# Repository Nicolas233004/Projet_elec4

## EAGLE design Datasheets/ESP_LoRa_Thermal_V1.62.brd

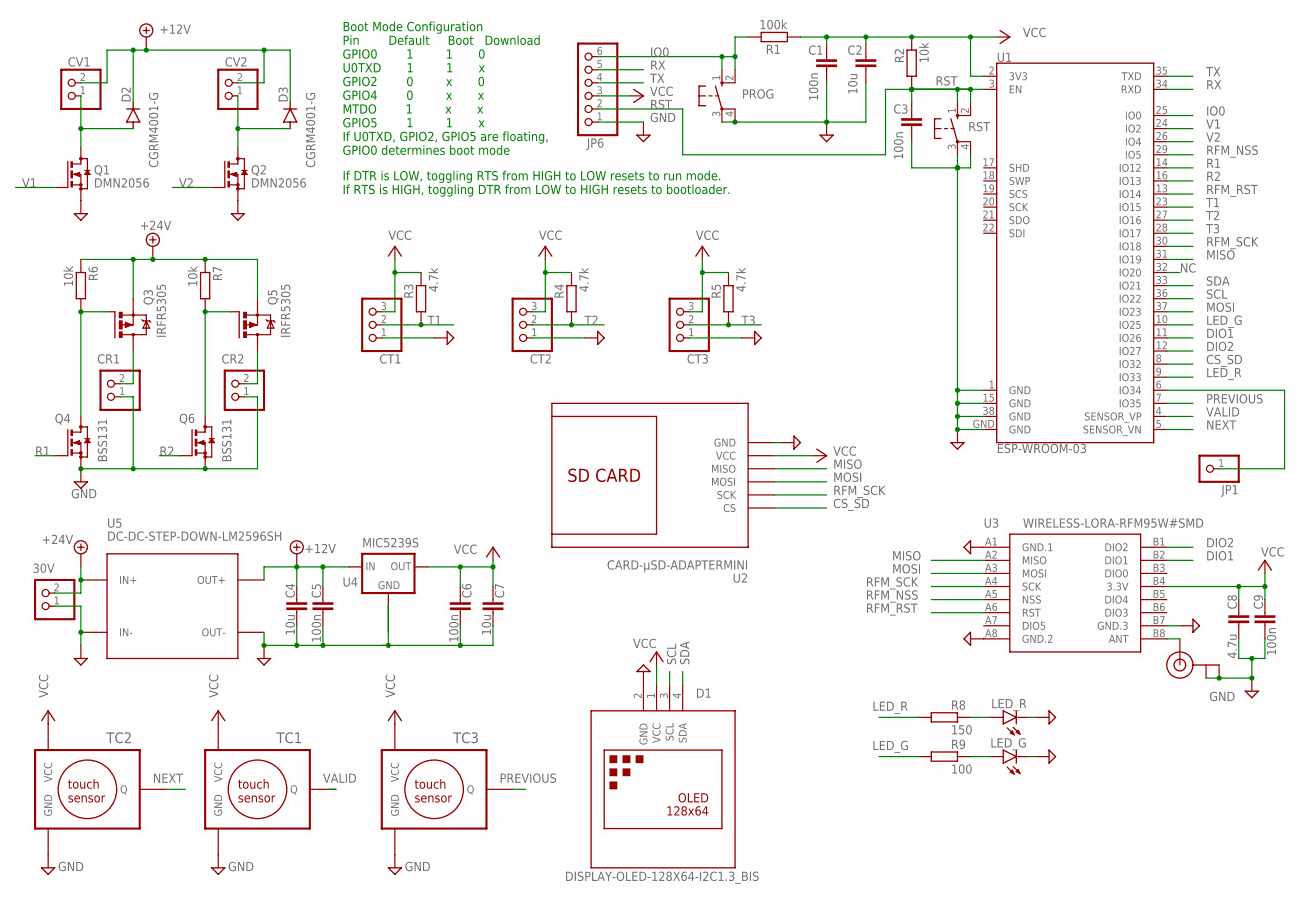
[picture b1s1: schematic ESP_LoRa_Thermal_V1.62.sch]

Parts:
30V: PINHD-1X2; 1X02
C1, C3, C5, C6, C9: 100n; C1206
C2, C4, C7: 10u; C1206
C8: 4.7u; C1206
CR1, CR2: PINHD-1X2; 1X02
CT1, CT2, CT3: PINHD-1X3; 1X03
CV1, CV2: PINHD-1X2; 1X02
D1: DISPLAY-OLED-128X64-I2C1.3_BIS; DISPLAY-OLED-128X64-1.3-I2C_BIS
D2, D3: CGRM4001-G; SOD-123_MINI-SMA
J1: U.FL
JP1: PINHD-1X1; 1X01
JP6: PINHD-1X6; 1X06
LED_G: LEDSMT1206; 1206
LED_R: LEDSMT1206; 1206
PROG: 10-XX; B3F-10XX
Q1, Q2: DMN2056; SOT23
Q3, Q5: IRFR5305; D-PAK_TO252AA
Q4, Q6: BSS131; SOT23
R1: 100k; R1206
R2, R6, R7: 10k; R1206
R3, R4, R5: 4.7k; R1206
R8: 150; R1206
R9: 100; R1206
RST: 10-XX; B3F-10XX
TC1, TC2, TC3: TTP223R_H; TTP233RED_H
U1: ESP-WROOM-03
U2: CARD-µSD-ADAPTERMINI; CARD-MINI--µSD-READER
U3: WIRELESS-LORA-RFM95W#SMD
U4: MIC5239S; SOT223
U5: DC-DC-STEP-DOWN-LM2596SH; DC-DC-STEP-DOWN-LM2596-SH

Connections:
+12V: C4.1, C5.1, CV1.2, CV2.2, D2.C, D3.C, U4.1 (IN), U5.OUT+
+24V: 30V.2, Q3.3 (S), Q5.3 (S), R6.1, R7.1, U5.IN+
ANT: J1.3 (SIGNAL), U3.B8 (ANT)
CS_SD: U1.8 (IO32), U2.CS
DIO1: U1.11 (IO26), U3.B2 (DIO1)
DIO2: U1.12 (IO27), U3.B1 (DIO2)
GND: 30V.1, C1.2, C2.2, C3.2, C4.2, C5.2, C6.2, C7.2, C8.2, C9.2, CR1.1, CR2.1, CT1.1, CT2.1, CT3.1, D1.2 (GND), J1.1 (GND), J1.2 (GND), JP6.1, LED_G.C, LED_R.C, PROG.3, PROG.4 (P1), Q1.2 (S), Q2.2 (S), Q4.2 (S), Q6.2 (S), RST.3, RST.4 (P1), TC1.P$3 (GND), TC2.P$3 (GND), TC3.P$3 (GND), U1.1 (GND), U1.15 (GND), U1.38 (GND), U1.GND, U2.GND, U3.A1 (GND.1), U3.A8 (GND.2), U3.B7 (GND.3), U4.2 (GND), U4.4 (GND), U5.IN-, U5.OUT-
IO0: JP6.6, PROG.1 (S), PROG.2 (S1), R1.2, U1.25 (IO0)
LED_G: R9.1, U1.10 (IO25)
LED_R: R8.1, U1.9 (IO33)
MISO: U1.31 (IO19), U2.MISO, U3.A2 (MISO)
MOSI: U1.37 (IO23), U2.MOSI, U3.A3 (MOSI)
unnamed: CR2.2, Q5.4 (D)
unnamed: CV1.1, D2.A, Q1.3 (D)
unnamed: CR1.2, Q3.4 (D)
unnamed: CV2.1, D3.A, Q2.3 (D)
unnamed: JP1.1, U1.6 (IO34)
unnamed: LED_R.A, R8.2
unnamed: LED_G.A, R9.2
unnamed: Q3.1 (G), Q4.3 (D), R6.2
unnamed: Q5.1 (G), Q6.3 (D), R7.2
NC: U1.32 (IO20)
NEXT: TC2.P$2 (Q), U1.5 (SENSOR_VN)
PREVIOUS: TC3.P$2 (Q), U1.7 (IO35)
R1: Q4.1 (G), U1.14 (IO12)
R2: Q6.1 (G), U1.16 (IO13)
RFM_NSS: U1.29 (IO5), U3.A5 (NSS)
RFM_RST: U1.13 (IO14), U3.A6 (RST)
RFM_SCK: U1.30 (IO18), U2.SCK, U3.A4 (SCK)
RST: C3.1, JP6.2, R2.1, RST.1 (S), RST.2 (S1), U1.3 (EN)
RX: JP6.5, U1.34 (RXD)
SCL: D1.3 (SCL), U1.36 (IO22)
SDA: D1.4 (SDA), U1.33 (IO21)
T1: CT1.2, R3.1, U1.23 (IO15)
T2: CT2.2, R4.1, U1.27 (IO16)
T3: CT3.2, R5.1, U1.28 (IO17)
TX: JP6.4, U1.35 (TXD)
V1: Q1.1 (G), U1.24 (IO2)
V2: Q2.1 (G), U1.26 (IO4)
VALID: TC1.P$2 (Q), U1.4 (SENSOR_VP)
VCC: C1.1, C2.1, C6.1, C7.1, C8.1, C9.1, CT1.3, CT2.3, CT3.3, D1.1 (VCC), JP6.3, R1.1, R2.2, R3.2, R4.2, R5.2, TC1.P$1 (VCC), TC2.P$1 (VCC), TC3.P$1 (VCC), U1.2 (3V3), U2.VCC, U3.B4 (3.3V), U4.3 (OUT)

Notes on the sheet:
If DTR is LOW, toggling RTS from HIGH to LOW resets to run mode. If RTS is HIGH, toggling DTR from LOW to HIGH resets to bootloader.
Boot Mode Configuration Pin Default Boot Download GPIO0 1 1 0 U0TXD 1 1 x GPIO2 0 x 0 GPIO4 0 x x MTDO 1 x x GPIO5 1 1 x If U0TXD, GPIO2, GPIO5 are floating, GPIO0 determines boot mode

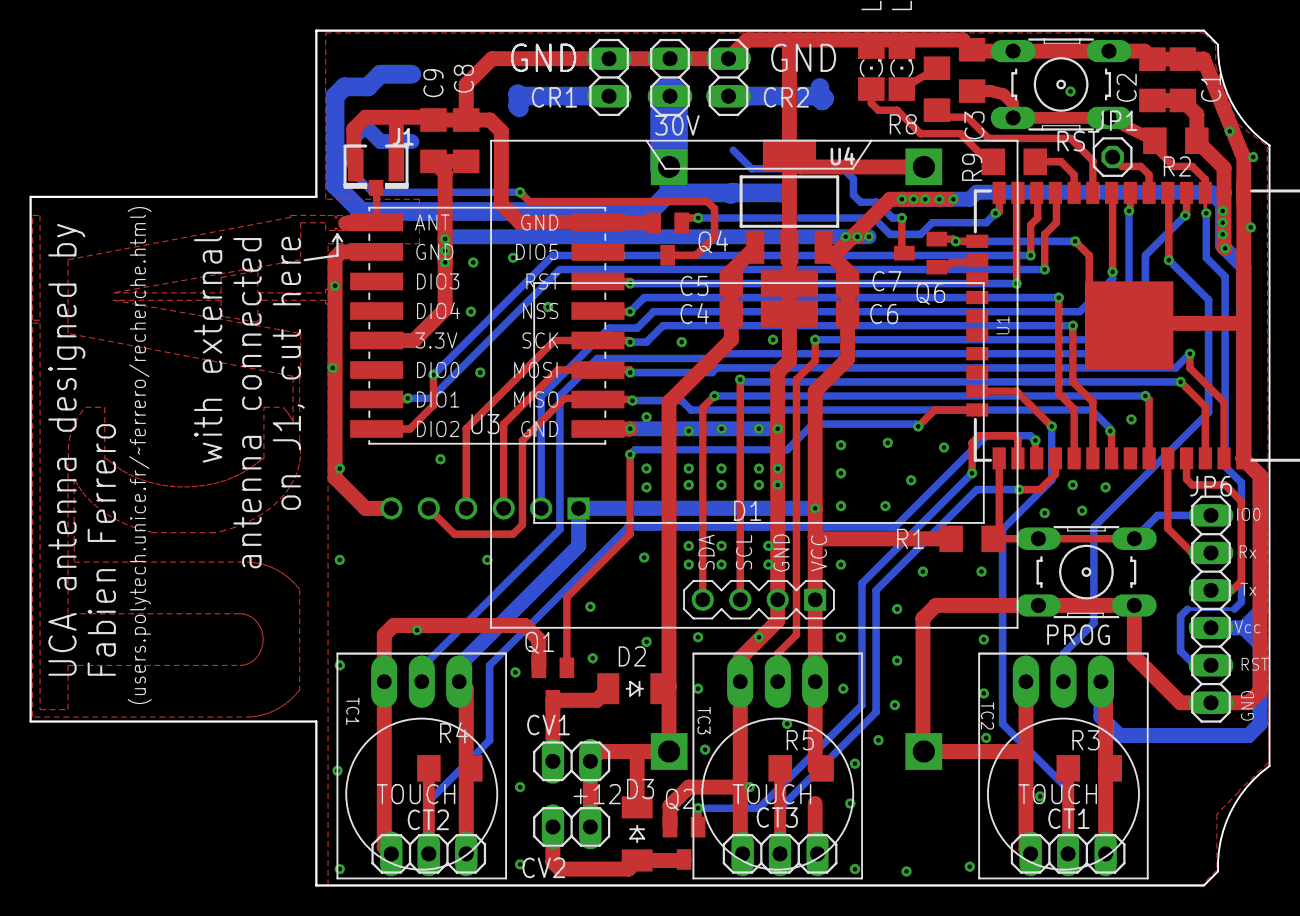
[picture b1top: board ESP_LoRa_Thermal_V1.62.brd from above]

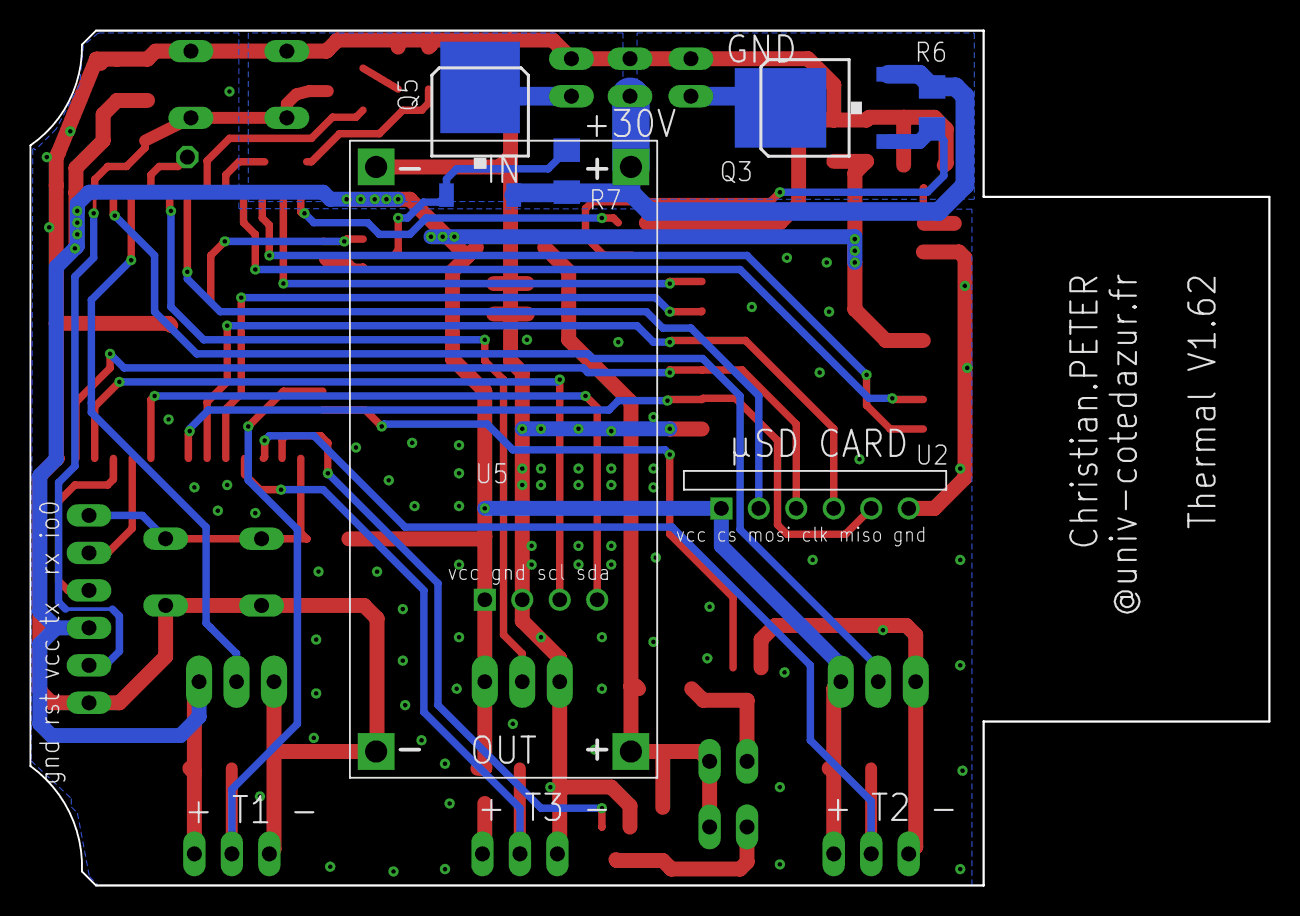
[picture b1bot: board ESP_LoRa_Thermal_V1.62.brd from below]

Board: 2 copper layers, 84.0 x 57.9 mm, 50 parts (6 on the bottom side), 40 nets.

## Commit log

2025-10-08 ajout ds18b20 datasheets
2025-10-08 ajout code ds18b20
2025-10-08 Create Rapport1
2025-10-23 Update preparation section for next session
2025-10-23 Create Abdoulaye
2025-10-23 Create Rapport Séance 1
2025-10-23 Rename Rapport Séance 1 to Rapport Séance 1.md
2025-10-24 Séance 1
2025-10-24 modif
    Removed redundant line for general objective.
2025-10-24 Séance2
2025-11-12 Séance3
2025-11-12 Séance4
2025-11-28 Séance 5
2025-12-11 Add Rapport Séance 1 documenting project progress
    Document the initial project setup and actions taken.
2025-12-11 Add report for Session 2 activities
    Document progress and activities for Session 2, including cleaning the model, installing Micro-Cap 12, and updating GitHub with datasheets.
2025-12-11 Create Rapport séance 3
2025-12-11 Rename Rapport séance 3 to Rapport séance 3.md
2025-12-11 Add session report for Séance 4
    Document the activities and progress made during the fourth session, including PCB modifications and preparations for future tests.
2025-12-11 Séance 6
    Document the objectives, proceedings, and conclusions of the sixth session regarding the heated beehive project, including issues with the circuit and components.
2025-12-11 Séance 7
2025-12-18 Create Rapport Seance 5
2025-12-18 Rename Rapport Seance 5 to Rapport Seance 5.md
2026-01-20 plans carte
2026-01-21 Create Rapport séance 8
2026-01-21 Rename Rapport séance 8 to Rapport séance 8.md
2026-01-21 Format markdown headings and add bullet points
2026-01-21 Revise formatting in Rapport séance 8
    Updated formatting for session report details.
2026-01-21 Fix header formatting in Rapport séance 8
    Updated the formatting of the session report header.
2026-01-21 Add Rapport séance 9 for Leandro Euphrasie
2026-01-21 Rename Rapport séance 9 to Rapport séance 9.md
2026-01-21 Update title format in Rapport séance 3
2026-02-03 Rapport Séance 8.md
2026-02-06 Rename Rapport10.md to Rapport_seance_10.md
2026-02-10 Add report for sessions 8 and 9
2026-02-10 Séance 10
2026-02-10 Update date for sessions 8 and 9
2026-02-10 Rename Séance2 to Séance 2
2026-02-19 Create Rapport de Séance 11
2026-02-19 Rename Rapport de Séance 11 to Rapport de Séance 11.md
2026-02-19 Rename Rapport de Séance 11.md to Rapport Séance 11.md
2026-02-19 Create rapport séance 12
2026-02-19 Rename rapport séance 12 to rapport séance 12.md
2026-02-19 Séance 11 et 12
2026-03-05 Create rapport_seance13
2026-03-05 Rename rapport_seance13 to rapport_seance13.md
2026-03-17 Create Rapport_seance14&15
2026-03-17 Rename Rapport_seance14&15 to Rapport_seance14&15.md
2026-03-17 Add report for Séance 13 on heating system project
    Document the objectives, process, and results of Séance 13 regarding the heating system for beehives, including modifications made to the filtering cell and ongoing issues.
2026-03-17 Add report for sessions 14 and 15 of beehive project
    Document the objectives, process, and outcomes of sessions 14 and 15 for the beehive heating project, including issues resolved and new sensor line added.
2026-04-03 Add session 16 report on thermal monitoring integration
    This report details the objectives, software updates, and conclusions of session 16, focusing on the integration of internal hive temperature monitoring.
2026-04-10 Séance 16
2026-04-10 Séance 17
2026-04-17 Ajout du code et du dossier eco
2026-04-17 Ajout dossier eco
2026-04-17 Ajout description projet
2026-04-17 Ajout fichier excel
2026-04-17 Analyse toit chauffant
2026-04-22 ajout Projet open LCA
2026-04-24 ajout Rapport All
2026-04-24 ajout Rapport fin de projet
2026-04-24 modif Rapport fin de projet
2026-04-24 Ajout dossier Code ecran
2026-04-24 ajout code ecran
2026-05-09 ajout diapo eco conception

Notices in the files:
parts and their libraries:
diy-modules: Released under the Creative Commons Attribution 4.0 International License: http://creativecommons.org/licenses/by/4.0
micrel: Copyright (C) 2008, Bob Starr
